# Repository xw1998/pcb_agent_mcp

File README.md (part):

# pcb-agent-mcp

**给硬件工程师和 PCB 设计者用的 MCP 服务器**：把「电路计算 + KiCad / 立创 EDA Pro 实操」接到 Claude、Cursor、Cherry Studio、Cline 等任何支持 **Model Context Protocol (MCP)** 的 AI 客户端上，让它在画板、选器件、跑 DRC、算载流与阻抗、对嘉立创（JLCPCB）工艺门禁时，给出来的是**量出来的数字**和**带闸门的写操作**，而不是背下来的经验。

> 检索关键词：PCB / EDA / MCP / Model Context Protocol / AI Agent / KiCad / 立创EDA / 嘉立创 / JLCPCB / 打样 / DRC / 阻抗 / 叠层 / 载流 / 温升 / 爬电距离 / IPC-2221 / 磁芯选型 / 环路与热 / 原理图 / Gerber。
> 全部在你自己机器上跑（唯一的出网是可选的立创在线取件查询，关掉就走本地 SQLite），零运行时依赖，Python ≥ 3.9。

> **这是 source-available（源码可见），不是 OSI 认证的开源软件。**
> **`0.1.43` 是本项目第一次对外发布。** 仓库历史里那份 MIT `LICENSE` 是内部草稿期的遗留文本，**从未对外提供过任何副本，因而不构成对外授权**；MIT 不适用于本仓库的任何版本（见文末「License」）。
> 代码按 [PolyForm Noncommercial 1.0.0](LICENSE) 授权、**禁止任何商业用途**；文档按 [CC BY-NC-SA 4.0](https://creativecommons.org/licenses/by-nc-sa/4.0/deed.zh)；随包的第三方组件各有原许可（见 [THIRD-PARTY.md](THIRD-PARTY.md)）。
> 商业授权请开 [Issue](https://gitee.com/xw19981010/pcb_agent_mcp/issues) 或邮件 <1490588966@qq.com>；细则见文末「License」。

当前版本 **`0.1.43`**：**注册 266 个工具**（`tools/list` 默认只暴露 50 个入口，全量需 `PCB_AGENT_TOOLSET=all`）、**零 runtime 依赖**、Python ≥ 3.9。已实现十一层：只读的算/保真/适配/度量/仿真，一条**带闸门的写路径**（提案 → 落盘，两种格式；还能**分步落盘**，让人在 EDA 窗口里看着它一步步长出来并随时喊停），一个**会说不通在哪**的布线器，一套**外包给立创/板厂自己的裁判**的制造输出与原理图同步，以及一层**从 20 块真实好板子量出习惯、但绝不自己动手改板**的经验累积（[docs/94](docs/94-经验累积模块与语料.md)）。
立创侧的每条口径都以 **194 个真实 `.epro` 归档**为证据（[docs/13](docs/13-立创实测-真实存储与记录格式.md)）；
KiCad 侧的几何与规则对着厂商自己核过：13 块真实板的 DRC 对账（厂商报的 56 条全命中）、
412 个焊盘与 `pcbnew` 逐点对账 0 不一致（[docs/15](docs/15-对账-推导对着厂商判决.md)）。

## 三十秒上手

```bash
git clone https://gitee.com/xw19981010/pcb_agent_mcp.git
cd pcb_agent_mcp
python run_server.py --version    # pcb-agent-mcp 0.1.43
python run_server.py              # 起 stdio MCP 服务（日志只写 stderr，stdout 归协议）
```

MCP 客户端（stdio）配置 —— 把路径换成你自己的绝对路径：

```json
{
  "mcpServers": {
    "pcb-agent": {
      "command": "python",
      "args": ["D:/path/to/pcb_agent_mcp/run_server.py"]
    }
  }
}
```

连上之后先调 **`calc_capabilities`**：它逐条列出「能算什么 / 拒算什么、为什么」，比任何文档都准，
也是本项目唯一不会过期的能力清单。完整自检与全量测试见[「用法」](#用法)。

## 本文目录

- 一页速查：做完了什么 / 还差什么
- 为什么不是"又一个图元 MCP"
- 三条诚实规则（代码里强制，不是口号）
- 为什么要内置计算：两个真实反例
- 信封契约
- 工具（266 个，默认入口 50 个）
- JLCPCB 制板门禁
- 用法
- 路线图
- 已知未实现 / 已打折扣的地方（诚实清单）
- 项目结构
- 第三方组件与商标
- 免责声明
- 贡献
- License

> **只想判断「现在能不能用」？** 直接看下面隔一节的
> **「一页速查：做完了什么 / 还差什么」**——三十秒扫完；本表是逐层机制。

| 层 | 做什么 | 状态 |
|---|---|---|
| **Calc** | 无板子的工程计算（载流/电流场/阻抗/差分阻抗/λ/20/爬电） | 已实现 |
| **Fidelity** | 把整份板文件**转换**成 AI 可读的表达：每个节点都进树，事实从树里读，往返由 KiCad 自己验证 | 已实现（KiCad 侧已被 kicad-cli 判决） |
| **Adapter** | 在保真树之上给一个 Canonical 便利视图（mm、Y 上、net 用名字） | 已实现（KiCad 侧：13 块真实板与 DRC 对账、412 个 pad 与 `pcbnew` 逐点对账；立创侧：194 个真实归档实测） |
| **Oracle** | 在解析出的板子上做度量（clearance / free_space / 铺铜连通 / 跨分割 / 环路面积 / 单网 IR drop） | 已实现 |
| **Sim** | 无板子的物理计算：SPICE 子集（DC/瞬态/AC）、铜阻与 PDN、热阻与 2-D 板温度、薄板模态与振动响应、平面谐振、电热耦合（单集中 Rth） | 已实现（子集，未实现项逐条点名拒绝（`0.0.37` 起 `A` 卡由随包 ngspice 承担；`0.0.39` 起 `gain`/`limit`、`0.0.40` 起多端口的 `summer`/`mult` 这四种代数 code model 由内置自己解） |
| **Desktop** | 找得到/启得动/关得掉 EDA，能打开工程并用窗口标题确认 | 已实现 |
| **Write** | `propose`（只算不写）→ `apply`（checkpoint + 原子写 + 六道闸门 + 失败回滚） | 已实现（KiCad 真机验证；`.epro` 实测口径＝原地重写一个成员，`0.0.62` 起**写出的归档再喂回应用并回读几何**验证过；`0.0.95` 起 **40 个 op**：`set_zone_params` 改铺铜的**填充参数**（`filled_areas_thickness` / `clearance` / `min_thickness`）并作废旧填充；`delete_copper` 按 net / layer / region 批量清铜；`dry_run` 走同一条写入+门禁+还原的路径试穿一次；DRC 差集的**两半对着同一份 `.kicad_pro`** 读——同一份字节，旁边没有工程文件时 515 error、有工程文件时 0 error，见 [CHANGELOG 0.0.95](CHANGELOG.md)） |
| **Route** | `board_route`：A* 布线（双栅格 + 精确多边形判决 + 事务化 + 按位置 rip-up），规则只从板/工程/调用方取，取不到就拒绝 | 已实现（50 网真板 baseline 27/50 → sweep+rip 38/50、端到端 apply 后 kicad-cli DRC 0 新增阻断项、12 网提速 5.5×；`0.0.15` 起爬电/差分对间距/等长进搜索，`0.0.16` 起回流/阻抗目标/拥塞协商也进了（协商默认关，一块板 +3 网 / +61% 时间），`0.0.17` 铺铜重填与多端网拓扑，`0.0.18` 起布不通要报**挡路的是谁**（`board_blockers`）与**哪些球埋着**（`board_fanout`）；`0.0.90` 起**锁定的铜不动**（文件里的 `(locked)` 或调用方的 `fixed_nets`：不布、不撕、不耦合/不等长——那两个 pass 要 MOVE 铜，所以是**拒绝**而不是悄悄剔掉，且无铜的固定网报 `fixed_missing_copper`），写路径对锁定铜要 `allow_fixed=true` 才动；`0.0.91` 起**悬空铜可查可切**（`board_dangling_copper`：只在「一个附着点 + 不是任何 pad 的唯一铜」被证明后才切，浮铜默认不动、锁定铜一律不动、没铺铜 fill 就如实说不猜；`0.0.92` 起在真板上把它的前提修对——通孔焊盘跨层、底面不镜像，并加 `pad_trust` 闸门：焊盘位置是推导时只列候选不判可切），仍然四邻 + 4×45°、不拆已接受的扇出、拓扑默认 mst 且不是精确 RSMT） |
| **Fab** | 制造输出：Gerber / Excellon / 位置文件 / gbrjob / STEP / PDF / BOM / 网表 / 图形，加 `manifest.json` 与可选 `fab.zip` | 已实现（**只外包不重算**：`kicad-cli` 在临时目录里跑，产物**重新读一遍**验终止符 / 工具表 / 行数 / ISO-10303-21，不合格判 failed；真板 15 个产物 / 103 923 字节 / `fab.zip` 33 577 字节；`out_dir` 落在源目录里直接拒） |
| **Sync** | 原理图网表 ↔ 板：逐脚差集，再变成 op 交给写路径 | 已实现（两侧都用权威：KiCad 自己的网表器 + 板文件里的 pad net；缺封装只报 `needs_placement`，**没有诚实的默认位置**；`sync` 一个字节都不写） |
| **Experience** | 从真实好板子量出来的经验：`hard`（违反＝缺陷）/ `soft`（违背＝问一句）两条链，7 个闭集度量，候选永不自己升级 | 已实现（种子 7 条 active 随包发出：6 个真实工程、20 块板、16 522 段铜、12 805 个 via；数字由判板子的同一份代码量出；改板一条都不做。[docs/120](docs/120-方案与布局的积累.md) 起补上**入料口**：`experience_harvest` 用同一份代码量一块板，把读数写进 `observations`、把与 active 习惯相反的写成反例候选（本机实测：4 条观测、1 条反例），`experience_status` 报「几条 active / 几条候选没人确认 / 文件最后写入时间」——库活着还是不活着，从此是读数不是印象） |
| **Layout quality** | 布局的**连续**读数（间距节奏/朝向/对齐/留白/密度/簇分离），给参考集时给分位 | 已实现（[docs/121](docs/121-布局质量与拓扑.md)：因为 `board_drc` 只有通过/不通过，在「勉强合规到正常」那一片里判据是平的、没有梯度——`docs/117` 那块 clearance 0、isolated 0 却两面地之间**零缝合孔**的板就是证据。分位只在给了参考集时出现；无方向指标只报分布位置不报好坏；**参考集是同族副本时判不可用**（本机 3 个备份版本实测） |
| **Topology** | 先分区后坐标：谁和谁同一功能组、组间怎么连、电源往哪流 | 已实现（[docs/121](docs/121-布局质量与拓扑.md)：主控按焊盘扇出认（本机 `PA0/PA11/+3V3` 这种网名任何关键词表都盖不住），其余按网名命中数投票；只碰电源轨的算电源；认不出的就近并入（≤15 mm）否则如实列 `unclassified`；`flow` 从 power 做广度优先，连不上的报 `unreached`） |
| **Pour fragments / corner fitting** | 铺铜被切成几块、每块多大、相邻隔多远；以及「切角会撞到邻居时是跳过还是缩短」 | 已实现（[docs/124](docs/124-铺铜碎块与自适应倒角.md)：新增 `board_pour_fragments`（鞋带面积 + 最近顶点对间距，未灌铜报 `pour_not_filled` 而不是 0 块），`board_angle_audit` 的 `chamfer` 加了 `adaptive`（撞了就二分缩到最大可行切角，实测同一块板 5→7 个切角、2 个从 1.0 缩到 0.25）。实测数据：+3V3 的 8 个形状块灌铜后是 **14 块**，最大 15.37×2.30 mm、最小 0.44×0.70 mm，最近邻 8 mm —— 这是「靠铺铜连通 3.3V」在这块 2 层板上不成立的直接原因。工具不判断两块能否连，只给几何。第三件：`board_routability` 加 `width_scan_mm` 线宽阶梯，回答「最宽能出去多少」——同一块板上 U1.14/19/21 只能 **0.3**、P2.3/P2.5 只能 **0.25**，这就是「+3V3 全程 0.4」在这里被推翻的数字依据；顺带一条被测试纠正的错判：三面围铜不吃线宽，**走廊**才吃） |
| **Via legality** | 一个孔**法律上**放得下吗、余量多少、被什么挡住 | 已实现（[docs/126](docs/126-过孔选址.md)：`board_via_sites`。缝合那轮的代价是量出来的——16 个接地孤岛只有 4 块放得下 0.45 孔，其中 2 块撞进 PD13/PD14 走线，靠重建板子读 DRC 才发现。`net` 是关键参数：该网自己的铜不吃余量（孔就长在自己的线上），但钻孔间距是工艺规则、任何网都不豁免。`room_mm` = 最紧那条约束的余量，`limited_by` 指名是哪条。真板实测：U1 上边扇出处 441 个候选里 **16 个**合法、最大余量 0.325 mm（限制来自邻线，不是铺铜），下边 **40 个**/0.225 mm。铺铜**默认不算障碍**（灌铜会绕开新孔重切，孔落在别网平面上只是咬掉一块），但每个点报 `inside_pours` 说明会咬哪块；`pours_block=true` 恢复严格口径。不放置、不写板） |
| **Trunk feasibility** | 这一网的焊盘簇之间，主干到底**能走多宽**、卡在哪一格 | 已实现（[docs/127](docs/127-电源干线可行性.md)：`board_trunk_plan`。因为「38 个 +3V3 未连接」能报，「0.4 主干走不走得过去」没人能答——那时只能先猜 0.5、被 DRC 打回、再猜 0.3。做法：焊盘**单连接聚类**（一排焊盘是一块，不是 20 个零长走廊）→ 簇心最小生成树 → 每条边两侧 `band_mm` 栅格化，每格价值 `2·min(到别网铜 − 间距, 到板边 − 边距)` → 带内**最大瓶颈路径**（可绕开焊盘排、不可穿过），4 连通。真板 sky_star `+3V3`：45 焊盘 → **14 簇 13 条边**、单次 **9.2 s**，0.4 mm 主干在 **12/13** 条通道上有层能走（`track_mm=0.5` 就变 2 条不通）；最薄 `9->13` F.Cu **0.164**、`11->12` F.Cu **0.373**（改走 B.Cu）；`5->9` **双层封死**，`grid` 0.15 / 0.12 与 `band` 8.0 三次复核仍 `no_path`——那 18.19 mm 走廊里实有 509 段信号线、30 焊盘、15 过孔，该动布局不是走线。**粗栅格把宽度读窄**：`9->13` 在 0.25/0.15/0.12 下是 0.164/0.314/0.345，最坏丢 `≈0.7·grid`，所以细一档是复核手段；超出 `band_mm` 就什么都不说，`beyond_reach` 是上界不是测量值。不写路径、不选层） |
| **Teardrop room** | 每个焊盘角上**还有没有位置**放泪滴、最长能长到多少 | 已实现（[docs/128](docs/128-泪滴余量与最长泪滴.md)：`board_teardrop_room`。参考工程的 `PRIMITIVE/TEARDROP` 对象有 30 个，照着复刻的 sky_star 一个都没有——「照着画不像」里可量的就是这个。做法：走线端点落在同网焊盘上、且**另一端在焊盘外**才算角 → 方向取**走线自身**（不是质心连线）→ 起点取中心线**离开焊盘**那一点，宽度取该点的**弦** → 两条斜边与端帽按 `grid_mm` 采样，每点 `min(到别网铜 − 间距, 到板边 − 边距)`，最小值为 `room_mm`（负数是「放不下多少」），并指名卡住它的对象；`max_length_mm` 是整条包络仍合法的**最长长度**（0.1 mm 步进）。**同网铜不是障碍**（泪滴就长在自己的铜上），障碍集按网过滤。真板：**238 个角、234 个放得下、4 个不行**，默认 `limit=40` 单次 **5.2 s**；最紧 `R19.1` `room −0.100`（与 `+3V3` 只隔 0.05）。`pad_width` 是离开焊盘处的弦不是对角线——按对角线会把 45° 引出的 0.3×1.6 焊盘读成 1.6 宽、一整排排针判死。不画泪滴、不选 curve） |
| **Net gaps** | 一个网的铜**断成几块**、最近的两块**差多远、在哪一段** | 已实现（[docs/129](docs/129-网络的铜断成几块.md)：`board_net_gaps`。DRC 只给「unconnected 115」这一行总数，它数 ratsnest 边，不会说 `+3V3` 一个人占 38 条、断成 39 块、最近两块只差 0.05 mm。做法：把这一网的焊盘/走线/过孔**加上它自己铺铜的 filled_polygon**（`_items` 里没有铺铜，而铺过铜的板子最大的那一块铜就是它）当几何 → 段级并查集（走线的圆头宽度、多边形取边）→ 触碰/重叠/包含即连通 → 报每块的焊盘位号/包围盒 + 相邻两块的最小边到边距离和量它的那对线段。不给 `net` 就数全板，这就是与 DRC 的对照：`+3V3 38/38、AGND 9/9、$2N1188 6/6、VDDA 5/5` 全等，**GND 不等（4 vs 15）**——差的 11 条是只靠单个焊盘散热辐条挂住的铺铜岛，我的几何算一个导体、KiCad 不算，因此**过不过板子听 DRC，这个工具只回答在哪、差多远**。真板 `+3V3` 0.55 s、全板 1.65 s。不连线、不换层、不挪件） |
| **Cut-line capacity** | 一条线切下去，两半之间有几条通道、又有几条网**必须**跨过去（布局层面成不成立） | 已实现（[docs/125](docs/125-切线容量.md)：`board_cut_capacity`。「必须过的网数 > 通道总数」是画通不了的必要条件，不必等布线器。默认只数画出来的铜（焊盘/过孔/走线），**不算铺铜**——灌铜会绕着过去的线重切，算进去会让每条铺过铜的线都读成满；`sensitivity` 三档把这份代价摆出来。实测 sky_star：排针列 361 条通道 对 5 个必须过的网，**推翻了我自己「12 个网穿焊盘行是通道不够」的解释**——差两个数量级，堵点在焊盘逃逸宽度。不选网、不画线） |
| **Routing discipline** | 走线的**形状**（斜线/离网格/跨板长段/拐角/扇出）、**规矩**（线宽梯级与按角色取宽、过孔族、拐角风格）与**重画清单** | 已实现（[docs/122](docs/122-布线纪律与参考板距离.md)：3 个工具 `board_routing_profile` / `board_house_style` / `board_routing_violations`。实测被参考板推翻了三个假设——F412 的斜线占比 44% 低于生产板的 48%、绕行率 1.089 优于 1.258、拐角 96% 已是 45°；唯一巨大的差异是线宽梯级 1 级 vs 13 级。`board_house_style` 从参考板取**比例**不取毫米（0.10 mm 信号线不是 53 mm 板子的宽度），`clearance_room` 逐网给出「最宽能到多少」，加宽不了进 `blocked` 并说明要先挪邻居；差分对同宽。三者都不写盘、不布线） |
| **Patterns** | 已经做成过的**方案**（recipe：让某件事 work 的参数与步骤）与**布局**（layout：相对一个 anchor 的毫米偏移） | 已实现（[docs/120](docs/120-方案与布局的积累.md)，6 个工具：`pattern_add` 只写 candidate；`pattern_verify` 要 `confirm=true` + 理由 + 一条带 `from`/`reading` 的证据；参数不给来源直接拒；布局必须恰好一个 anchor；`pattern_layout_plan` 只算坐标并报冲突（越界 / 同一位号已在板上 / 小于 `min_gap_mm`），**不写板**——本服务没有自动布局，这是禁令不是待办） |

写路径的三条硬规则：**提案不落盘**（plan 单次使用、1 小时过期）；**落盘要 `confirm=true`**；
**闸门不信任写代码本身**——KiCad 侧是盘上字节、token 双射、每条 op 的后置条件、`kicad-cli` 的
stats/Gerber/贴片坐标比对、以及 **DRC 差集**（新增违规就拦下并回滚）；立创侧是写盘字节、其他成员
逐字节不变、未点名行不变、流仍可解析、改动恰好等于计划、重新解析后事实成立。
KiCad 侧这套闸门在自造示例板上真拦下过三次错（丝印压板边、悬空走线、悬空过孔）。

> 设计文档在 [`docs/`](docs/)，按编号顺序读：
> `00` 调研与架构 → `05` 无损转化架构总纲 → `06` 存储形式与信息传递 → `07` 自研定位与风险分期
> → `10` 桌面控制与双栈读路径 → `11` 保真层 → `12` 写路径 → `13` 立创实测（真实存储与记录格式）
> → `14` 原理图写路径 → `15` 对账（推导对着厂商判决）→ `16` 天线与馈线 → `17` 仿真层
> → `18` DFM 工艺能力校验 → `19` 机械振动（薄板 Ritz 模态、多模态随机响应、Steinberg、冲击、传递率）
> → `20` 平面谐振与电热耦合 → `22` 微带与腔体滤波器 → `24` 立创进程内桥
> → `25` 技能并入清单 → `26` 分步可见与铺铜闭环 → `27` 自动布线器。

## 一页速查：做完了什么 / 还差什么

这一节回答一个问题：**现在能不能用、哪一格还不能信。** 三十秒扫完；机制与数字在下面
「已知未实现 / 已打折扣的地方」与 `docs/` 对应篇目里。

判定口径只有一条：一个能力同时满足 ① 有工具 ② 有闸门或参照 ③ **有一条能失败的对照**
（负控制，或对着厂商判决的对账）才算「做完了」。只写了代码、没有对照的，一律算没做完。

### A ｜做完了（有工具、有对账、边界写在每次返回里）

| 能力 | 起于 | 凭什么说做完了 | 它自己的边界 |
|---|---|---|---|
| **工程计算**：载流 / 阻抗 / 差分 / λ/20 / 爬电 / 间隙 / 铜阻 / 电感 / 链路 | `0.0.1`，真实表 `0.0.10` | IEC 60664-1 阶梯从 KiCad 10.0 原实现反演，**188 528 点 0 失配**（32 键 / 808 步）；IPC-2152 用 Brooks & Adam 闭式 + 3 个独立锚点复现 | 闭式近似，误差进 `precision`；IEC 62368-1 / 61010-1 / UL 60950 / IPC-2221 仍 fail-closed |
| **二维场解**：差分截面 / 共面单线 / 共面差分对 / 有限宽地 / 导体损耗 | `0.0.19`~`0.0.26` | 零厚度带状线对精确共形解 ≤1.2%、孤立微带对 Hammerstad ≤2.8%；共面差分对无闭式，改用叠加恒等式（残差 1.9e-8）+ 奇模电荷平衡 −1.000000000 + 极限 | 紧间距耦合**没有独立参考答案**（回 `reference_note`）；铜厚只划网格不建模；共面解比闭式**读低 1.19%~3.39%** |
| **保真层**：整份文档进树，往返可证 | `0.0.1`（`0.0.18` 补口径） | KiCad 侧 token 双射 + 逐字节往返；立创侧 194 个真实 `.epro` 归档实测 | 13 块 demo 板覆盖不到的少见语法可能没走到 |
| **Adapter**：两份格式 → 一个 Canonical | `0.0.1` | 13 块真实板上与 `kicad-cli 10.0.7` 对账（厂商 56 条 recall 1.0）、412 pad / 20 188 次 HitTest / 0 不一致 | 立创焊盘位置是推导（顶面 62.1% / 底面 82.6% 落在本网铜端点上，是**下界**不是精度）；底面**不镜像**（`-y` 只有 37.0%/53.2%，异网误撞 1/2） |
| **Oracle 度量**：间距 / 可放空间 / 铺铜连通 / 跨分割 / 环路 / IR drop | `0.0.1` | 每条带 `authoritative:false` + 裁判在哪；能对账的间距项双向数 recall 与 extra | 三类几何**不建模**（zone 铜、板边与孔规则、阻焊钢网）；比不了的明确 `not_comparable` |
| **写路径**：提案 → 落盘 → 闸门 → 回滚（两种格式） | `0.0.1` | KiCad 五道闸门（含 DRC 差集）在自造板上**真拦下过三次错**；立创六道闸门，实测同一工程两次保存只改一个成员 | 立创原理图 `.esch`、SQLite `.eprj2` 一律拒写 |
| **原理图**：KiCad 单页 22 op + 多页 4 个 sheet op | `0.0.1` / `0.0.33` | 裁判换成 KiCad 自己的网表 + ERC 双向 diff；页号按**工程全局**分配 | 不做跨多文件原子写、页面模板、搬文件、批量重命名 |
| **布线器**：A* + 精确多边形判决 + 事务化 + 按位置 rip-up | `0.0.14`~`0.0.17` | 50 网真板 27/50 → 38/50（开协商 41/50）；端到端 apply 后 `kicad-cli DRC` 新增阻断项 = 0 | 四邻 + 4×45°、不拆已接受扇出、拓扑非精确 RSMT、拥塞协商默认关 |
| **制造输出与同步**：Gerber/Excellon/STEP/PDF/BOM/网表 + 原理图↔板差集 | `0.0.18` | 产物**重新读一遍**验终止符/工具表/行数/ISO-10303-21；`out_dir` 落在源目录里直接拒 | 只外包 `kicad-cli`，不重写 writer；`schematic_pcb_sync` 一个字节都不写 |
| **仿真（内置 SPICE）** | `0.0.7` 起，`0.0.27`~`0.0.39` 逐类长出来 | 器件 `R C L V I E G F H K D Q M B S W J` + `X`/`T`/`O`/`U` + `.noise` + `A` 的 `gain`/`limit`/`summer`/`mult`，每类都有对账（例：1 kΩ 读 `4.071372237e-09 = sqrt(4kT·1000)`） | 后向欧拉；无自热、无失真/傅里叶、无器件电容随温度；`A` 里只有四种纯代数 code model 进内置；1/f 只做**二极管**（`KF*|Id|^AF/f`，`Q`/`M`/`J` 的 `KF=` 在 `.noise` 按名拒答），`mc(...)` 这类统计值一律拒答，`.temp` 多值是扫描（`0.0.54`） |
| **仿真（外部引擎 + 随包）** | `0.0.7` → `0.0.37` 随包 | 真 ngspice-47 逐节点对账（分压 5e-9 V）；随包副本与系统副本六类 deck 差 0 ~ 1 ulp | 只 Windows x86_64；`engine="auto"` **刻意不看随包**；不做 DLL 进程内 |
| **热 / PDN / 振动 / 平面 / 电热** | `0.0.5`~`0.0.6`、`0.0.10` | 2-D 板温度 `73.393487 ℃` 对闭式 `73.39345`；Ritz 模态 SSSS 330.385 Hz、CCCC 602.382 Hz 与解析解吻合 | 1-D/2-D 稳态、薄板单模态、平面只有模频与导体/介质损耗的 Q 上界、电热单集中 `Rth` |
| **铺展（收缩）热阻**：板上的小焊盘比它自己那柱铜多出多少 | `0.0.85` | 两个极限是**手算恒等式**：整板 `t/(kA) = 0.05` 精确、对流整板 `0.05 + 1/(hA) = 10.05` 精确；另有一个**不分离变量**的三维 FVM 在 `dz` 逐档减半时差距 12.42→8.29→4.13→2.03→0.97 % 逐档减半；四条负控制（漏正交因子 >10 %、整板锚点对同一错法差 `0.0` 即**盲**、尺度错 >40 %、朴素径向式 >30 %） | 均匀热流而非等温焊盘（半空间上 8 %）、四侧绝热、单层平板；圆/环源、多层叠、热过孔、接触热阻、侧边对流都不在；薄板收敛慢（`t=1e-3 mm` 时 120 项仍差 0.85 %，答案随附 `convergence_rel`） |
| **熔断的潜热**：Onderdonk 只算到铜「到达 1083 °C」，可它还没熔 | `0.0.86` | 闭式 `β = L_f/(c(234+Tm)ln(ratio))`，几何/面积/`ρ20` 全消掉 ⇒ `I²t` **+25.3 %**、电流 **+11.9 %**（25 °C；0 °C +11.3 %、100 °C +14.0 %）；**不是**教科书的 `L_f/(c ΔT) = 0.512`——潜热阶段站在最热点上，`β/naive = (234+Tm)ln(ratio)/(Tm−Ta) = 2.0244`；五档 β 由**独立 RK4 积分同一条 ODE** 校验（相对差 1.8e-12 / 2.6e-15 / 1.5e-12 / 4.9e-12 / 2.6e-12）；`c=385` 由 `(cρ/ρ20)(234+25)` 与 `1/(CMIL²·33·ln10)` 的 **+1.34 %** 一致性定（400 会推到 +5.3 %） | 默认**关**（`melting_model="sensible"`），以前打印的熔断表**逐位不变**；`repetitive_pulse_rating` 的潜热已在 `0.0.87` 做掉，`fusing_current_taper` 在 `0.0.88` 做掉（每节点焓状态），所以三个熔断工具都带它；熔化后的体积变化与熔流、焊点合金化仍然都不在（`not_implemented_yet` 已从此前的「Melting, by name」改写为「Melting, past the melt-through」） |
| **脉冲串的潜热**：一串脉冲上的潜热，以及「可持续电流」原来答错了 | `0.0.87` | `repetitive_pulse_rating` 原来把 `i_crit = sqrt(A·h·P/(duty·β·rho))`（纯**速率平衡**，不含热容也不含熔点）当成「最大可持续电流」放在 `value` 里返回；0.0.87 把 `value` 改成真正的**不熔电流**（二分到峰值 1083 °C）：0.5 mm/1 oz/1 ms/5 % 是 **29.617434 A**，旧值 **33.156444 A**；**duty 1 %** 时旧值 **23.445147 A** 对新值 **5.284344 A** ⇒ **高报 4.436718 倍**。三段电流并存：`max_current_without_melting_a`（与潜热无关）、`max_repetitive_current_a`（旧值原样保留 + 明确标 *upper bound*）、`max_current_without_melt_through_a`（峰值可钉在 1083、靠停歇排空储层：A **29.717885** / C 5.581757 / D 5.881642，对不熔电流 **+0.34 %~+11.3 %**）。潜热在串上的效果：`latent_rise_k = L_f/c_p = **542.077922 K**`，0.95×runaway 处 81→**139** 发（+71.605 %）、274→**467**（+70.438 %），1.005×value 处 218→**2360**（+982.569 %），1.02×value 的 C/D **永不熔**；储层按**熔点处吸热速率** `φ = a(1+β·dTm) = 2155.3238 K/s` 灌满（`a = 423.8640 K/s`），绝热档的**额外通电时间** `(L_f/c_p)/φ = **0.251506 s**`（实测 0.05 s→5 发、0.01 s→25 发、0.005 s→51 发） | 默认**关**（`melting_model="sensible"`）时信封**逐位不变**（整信封相等有测试）；临界点逐发在 **1/n** 上收敛（B 组要 1e5 发）⇒ 解析值用**不动点二分**并与逐发暴力实现交叉验证；`max_repetitive_current_unaffected_by_latent=true` 是**真的**（它本就不含热容，潜热改不了它）；`fusing_current_taper` 的潜热在 `0.0.88` 补上；无 Stefan 前沿、无熔流与体积变化、无焊点合金化 |
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
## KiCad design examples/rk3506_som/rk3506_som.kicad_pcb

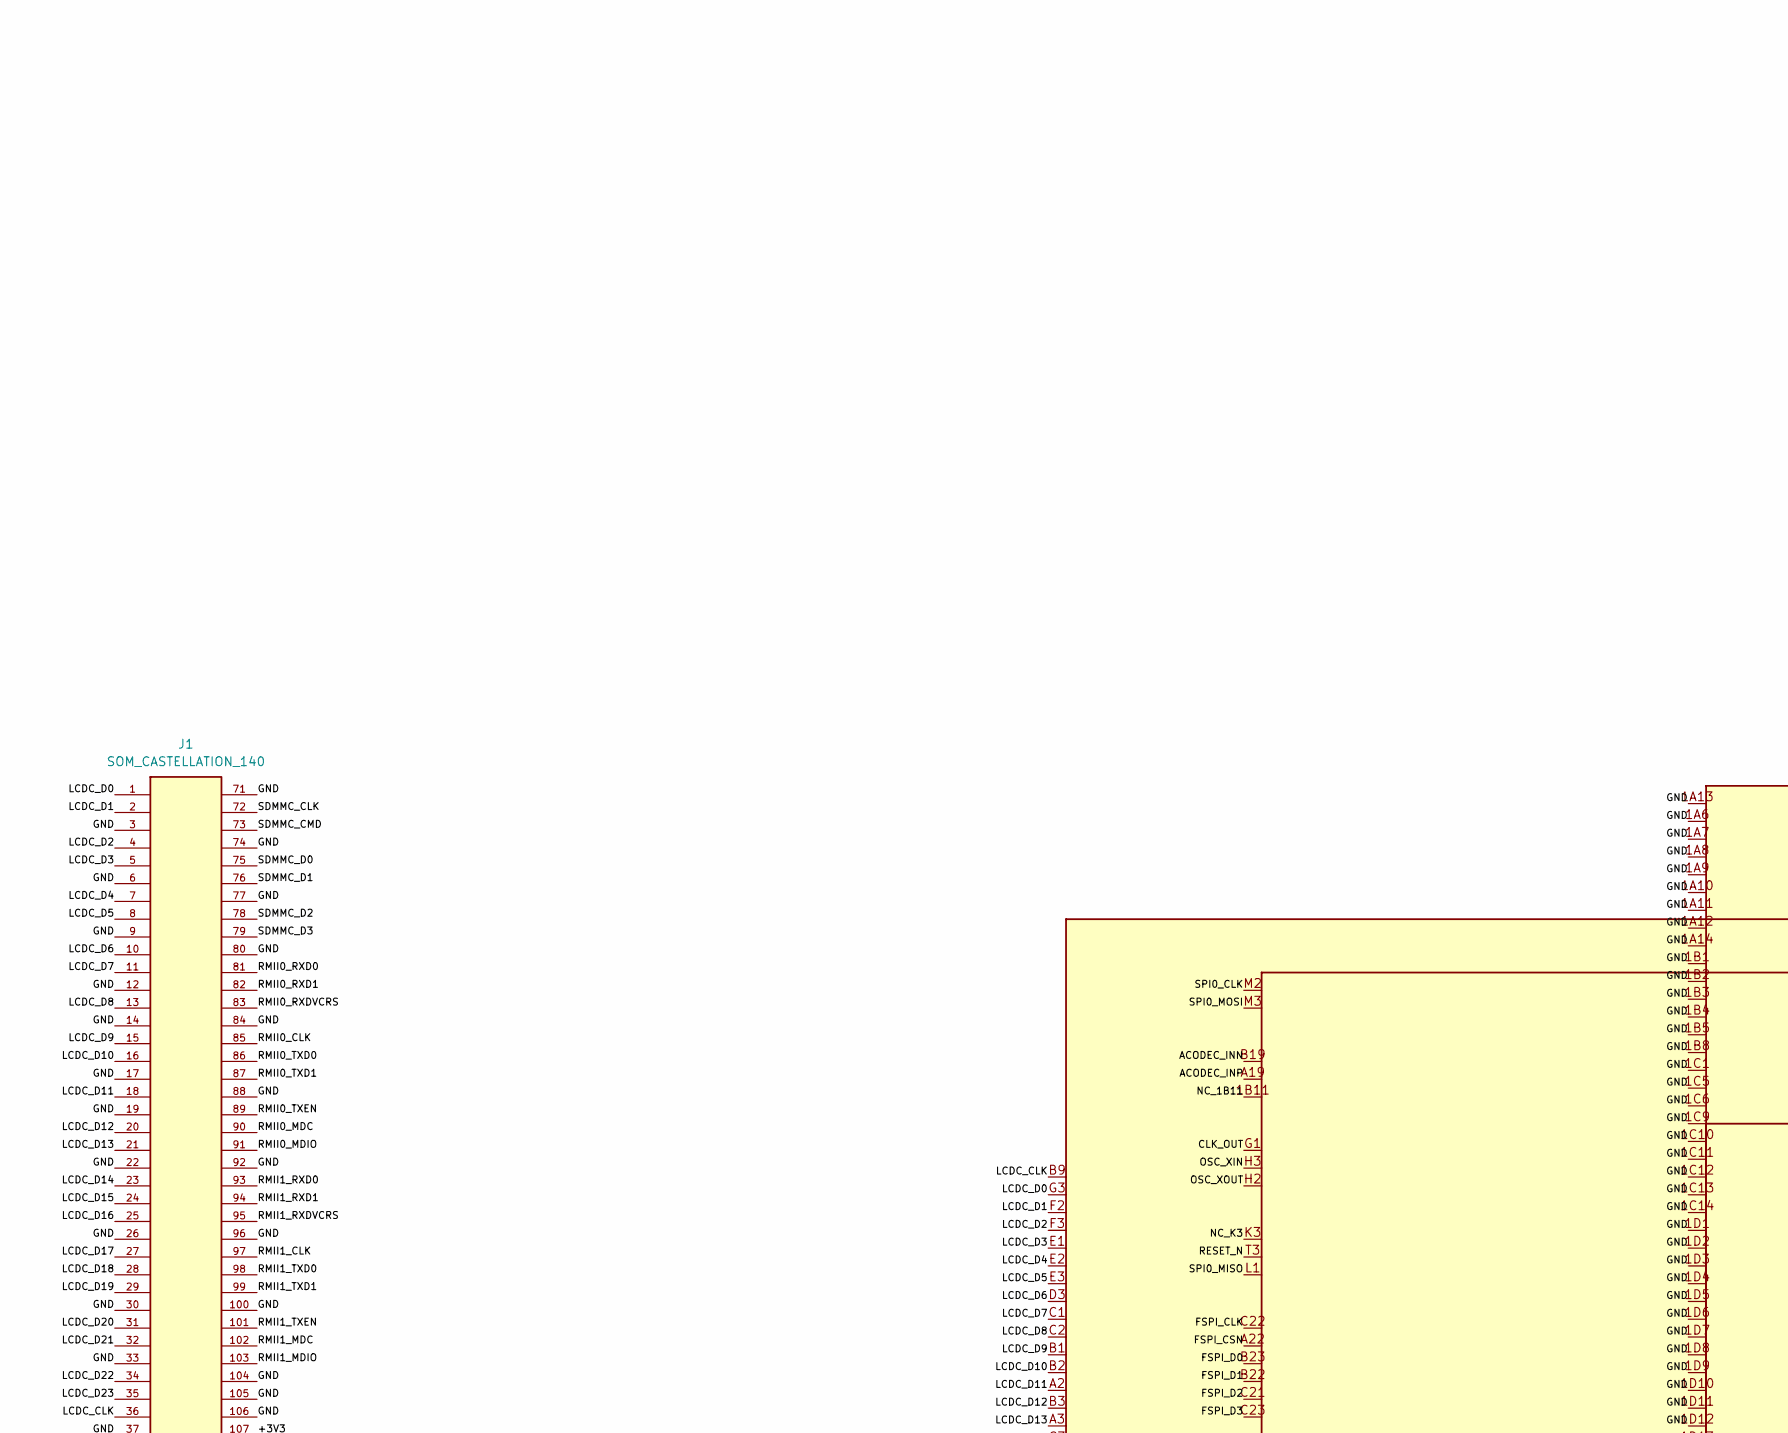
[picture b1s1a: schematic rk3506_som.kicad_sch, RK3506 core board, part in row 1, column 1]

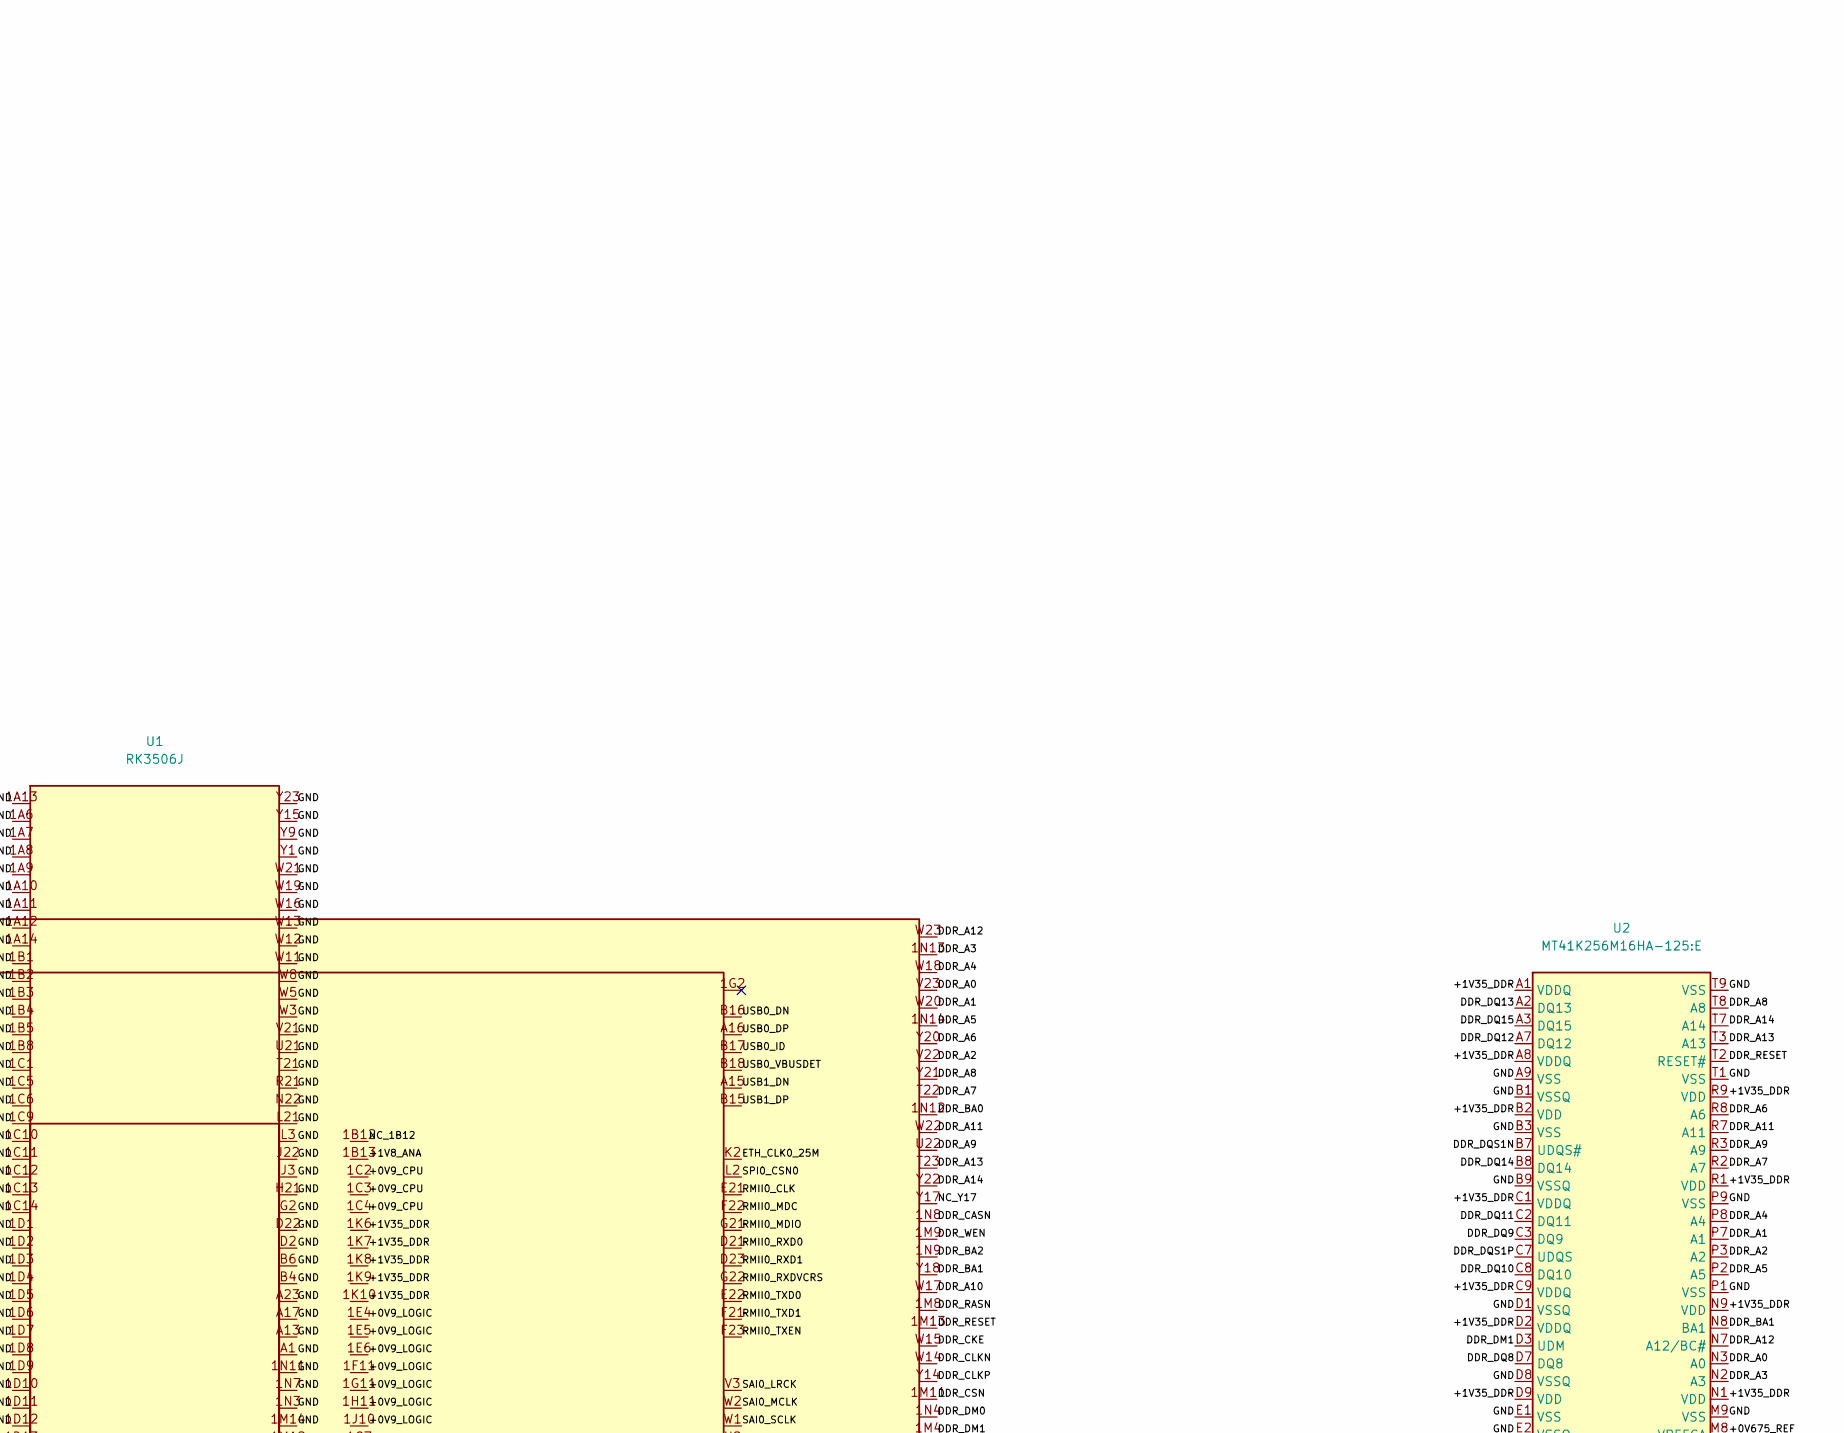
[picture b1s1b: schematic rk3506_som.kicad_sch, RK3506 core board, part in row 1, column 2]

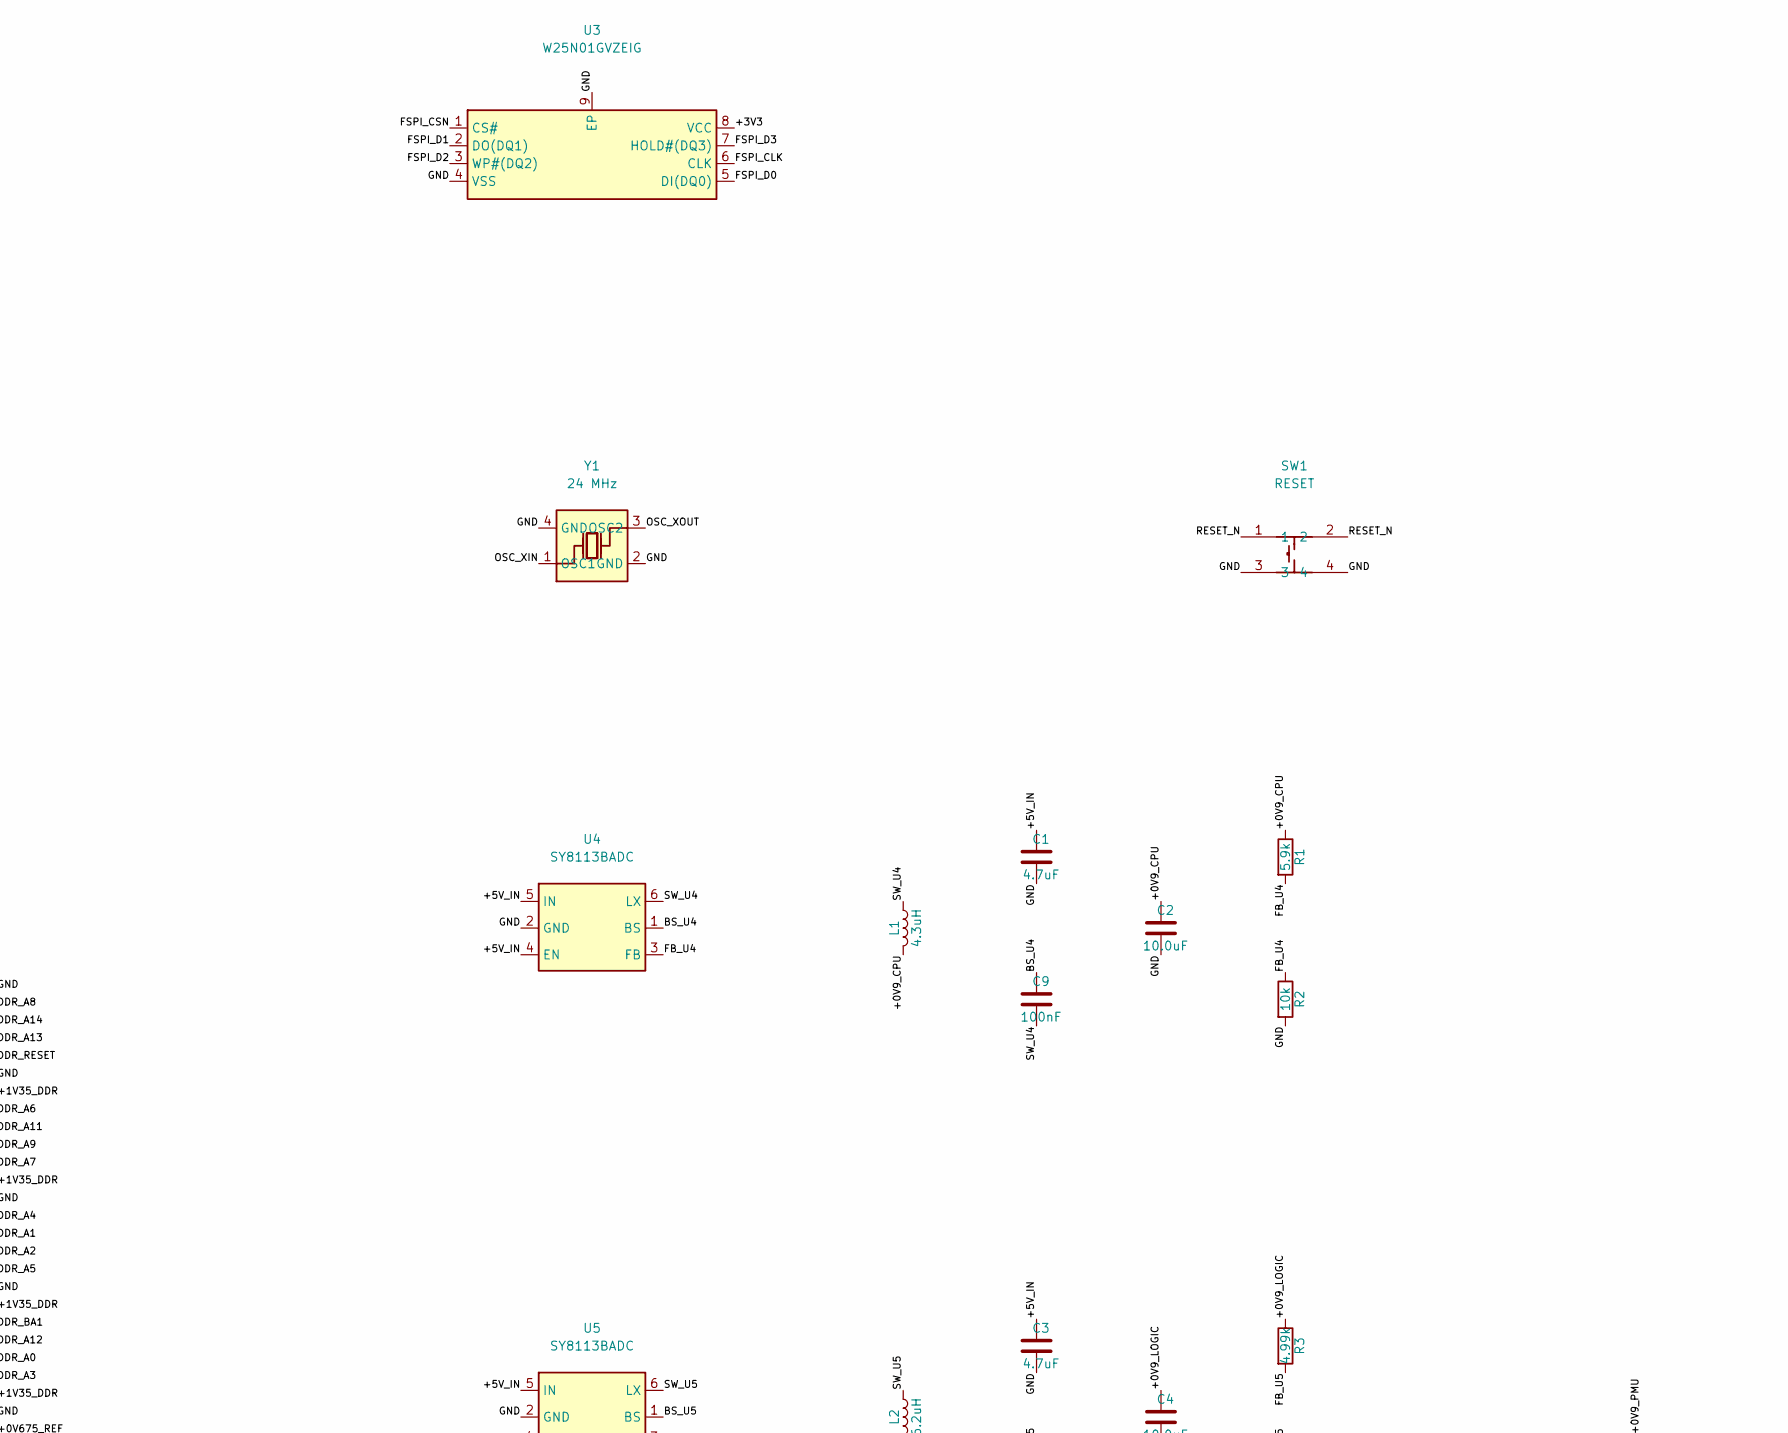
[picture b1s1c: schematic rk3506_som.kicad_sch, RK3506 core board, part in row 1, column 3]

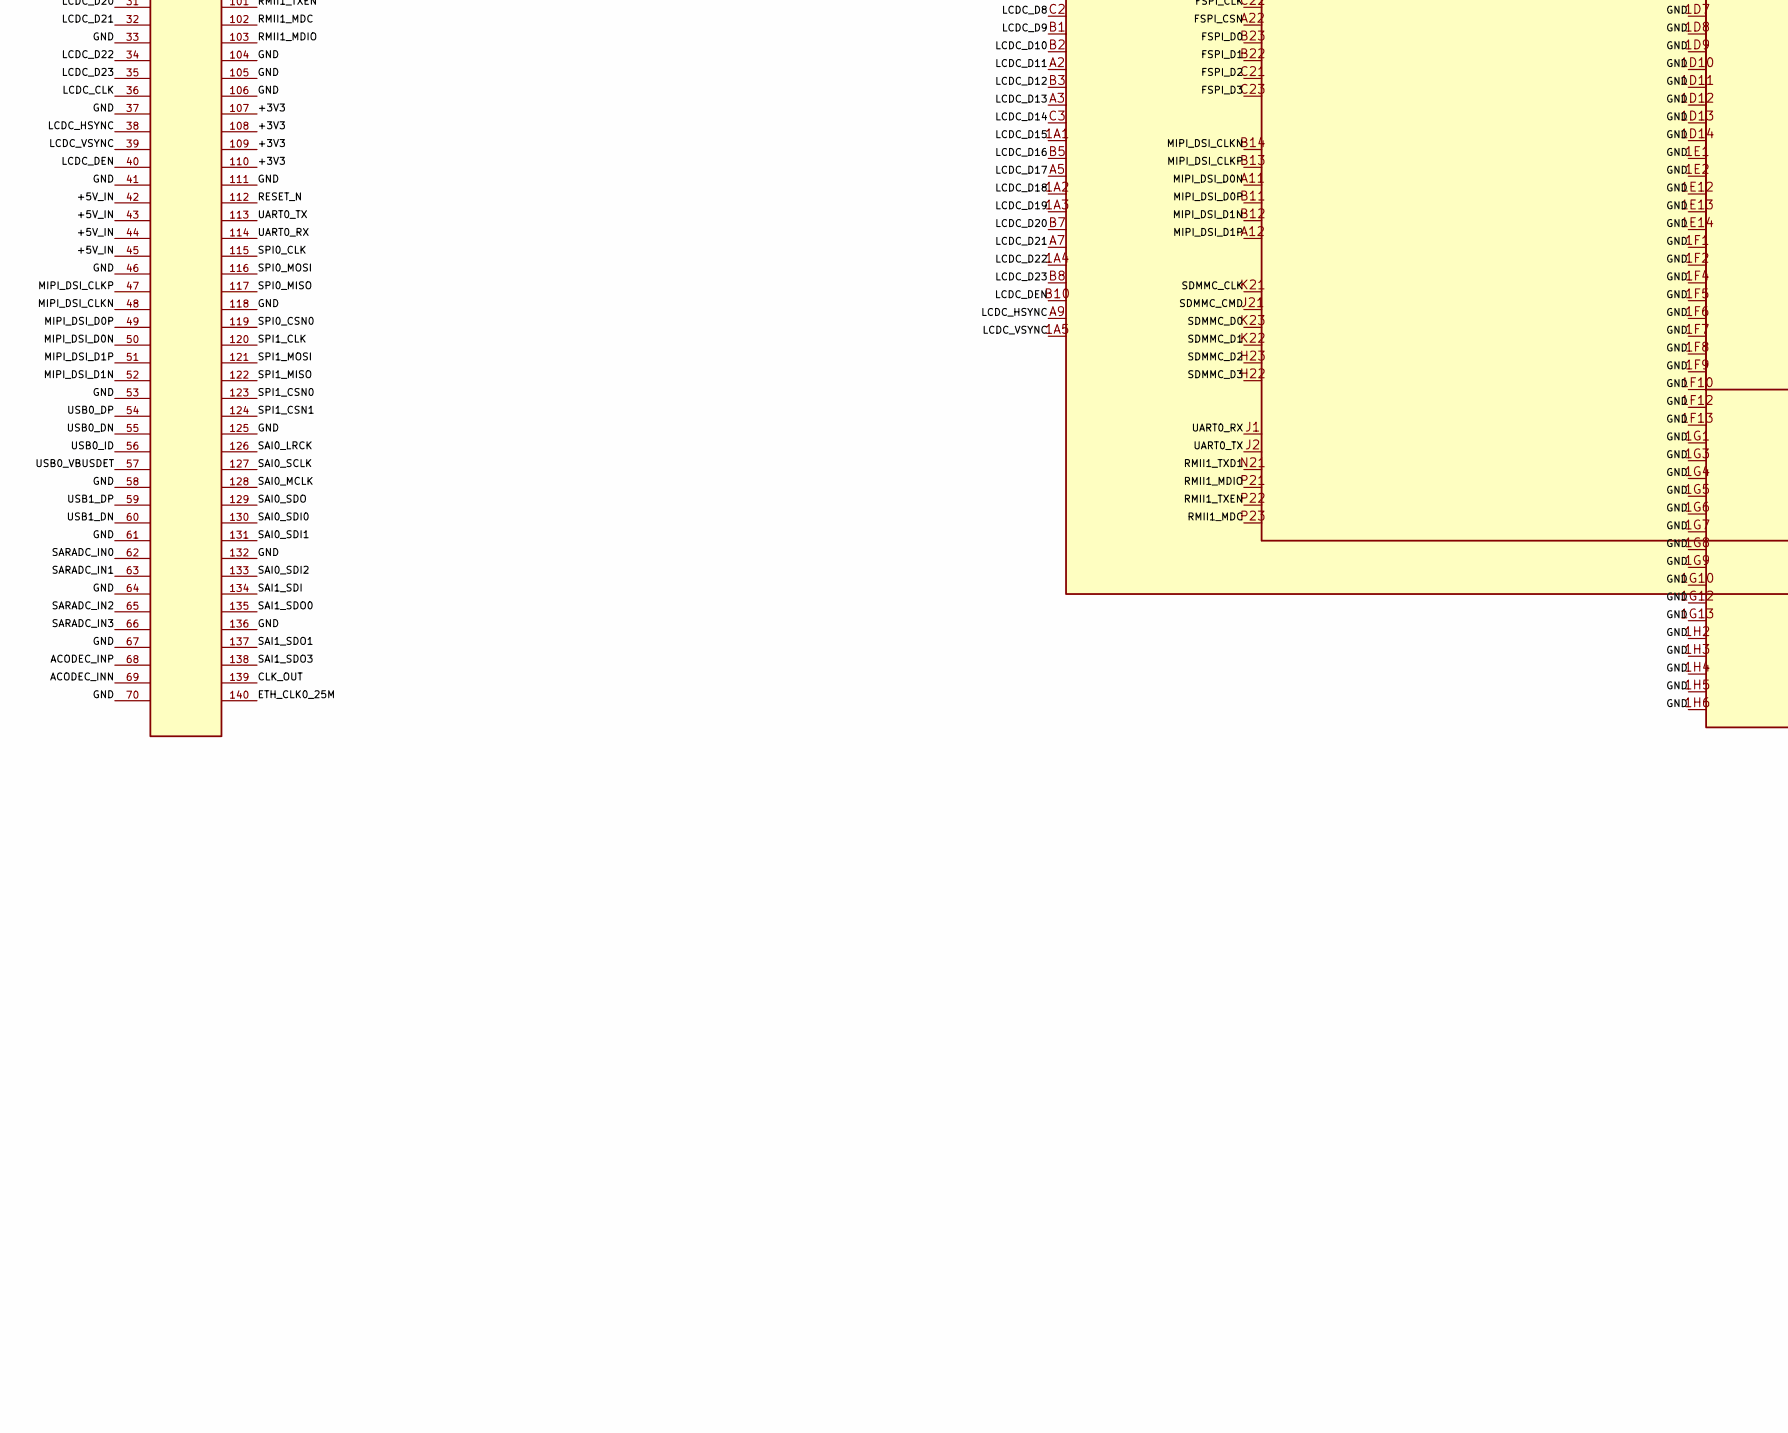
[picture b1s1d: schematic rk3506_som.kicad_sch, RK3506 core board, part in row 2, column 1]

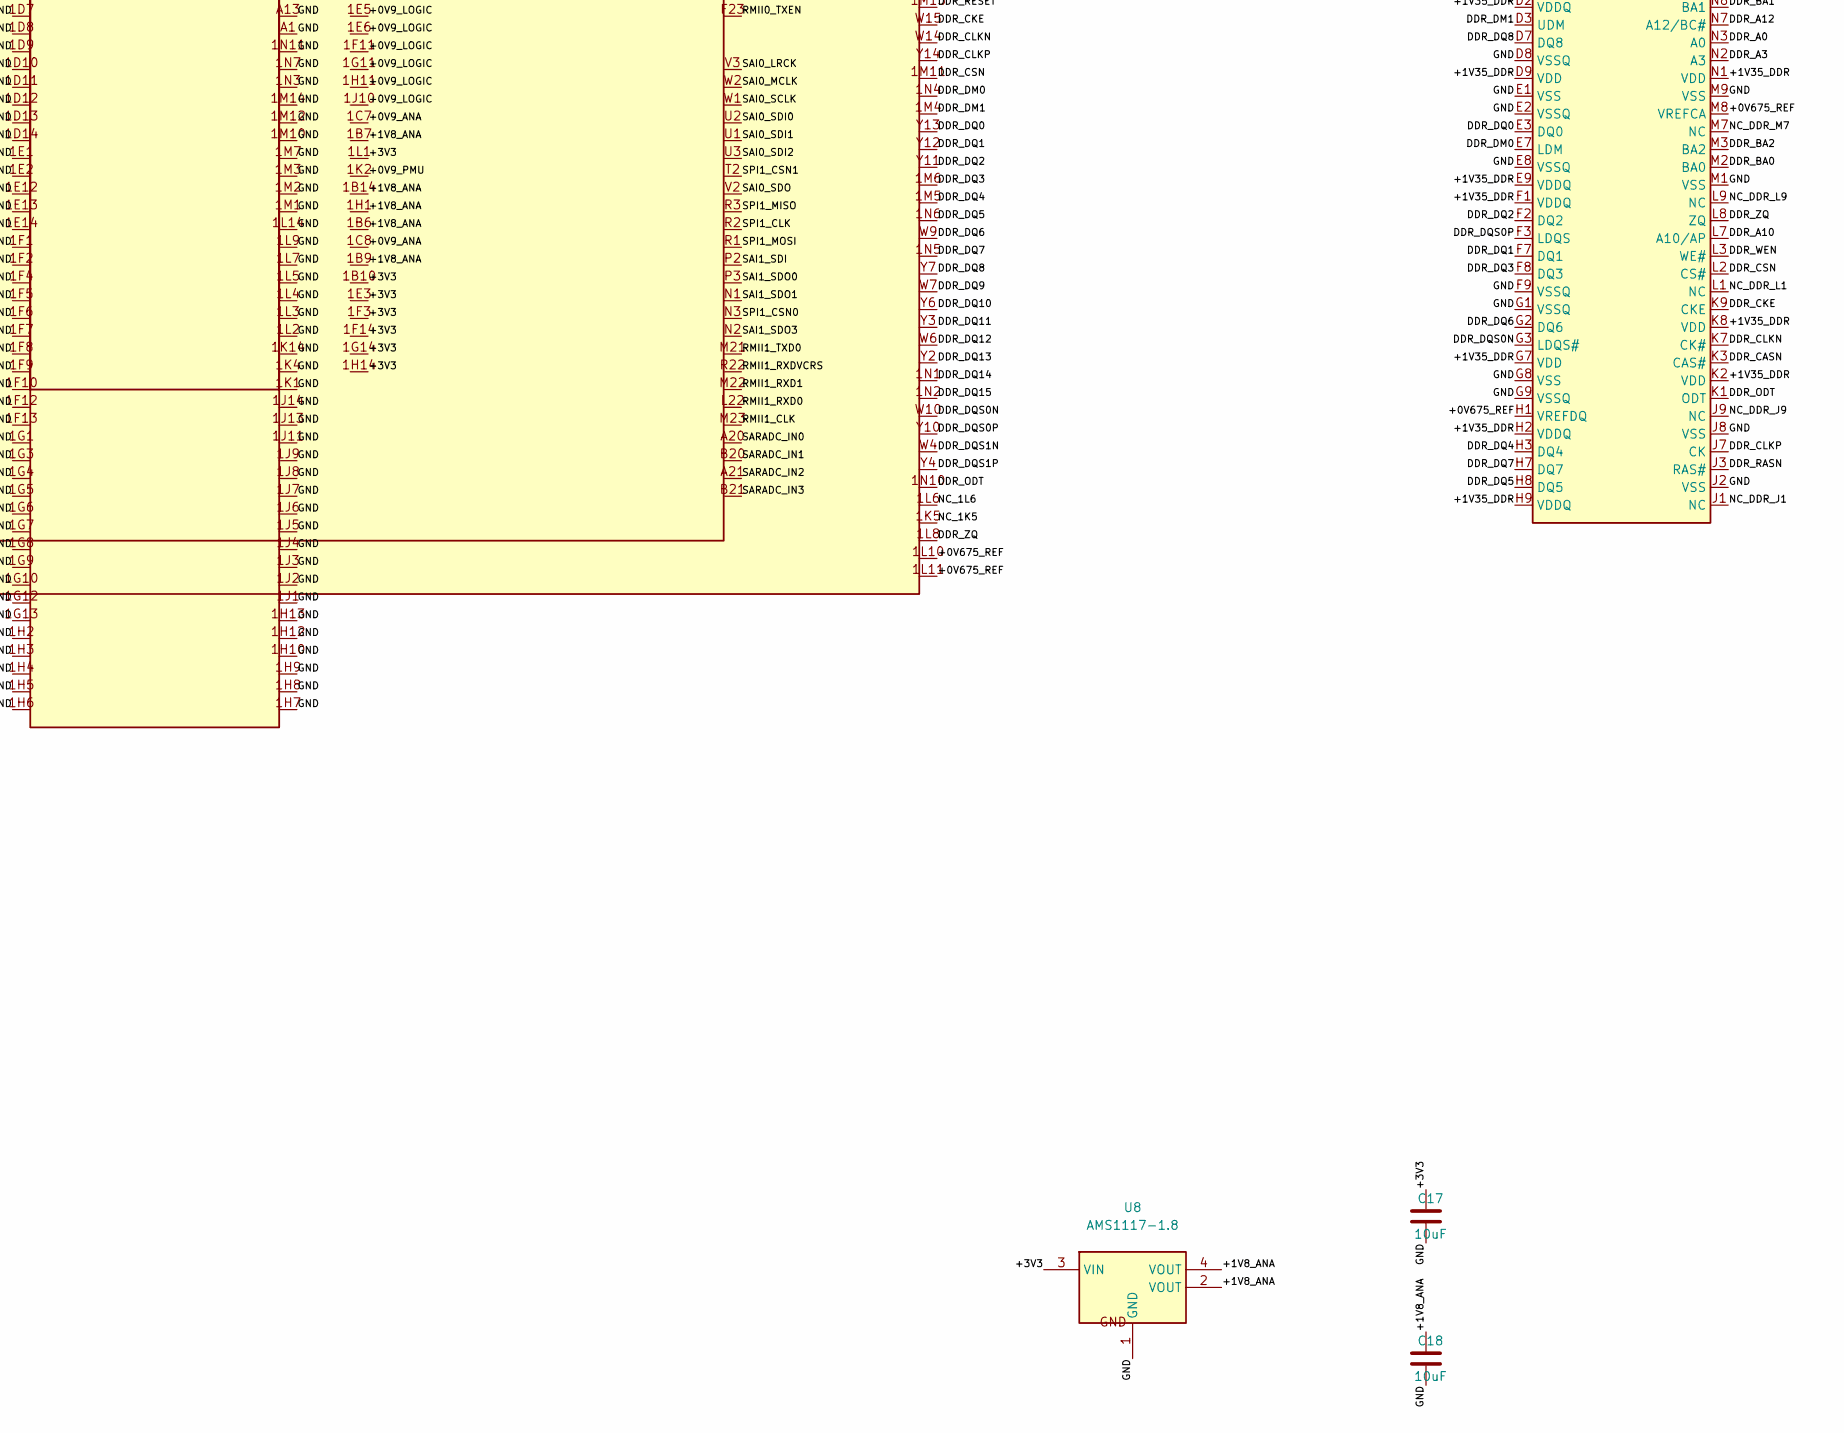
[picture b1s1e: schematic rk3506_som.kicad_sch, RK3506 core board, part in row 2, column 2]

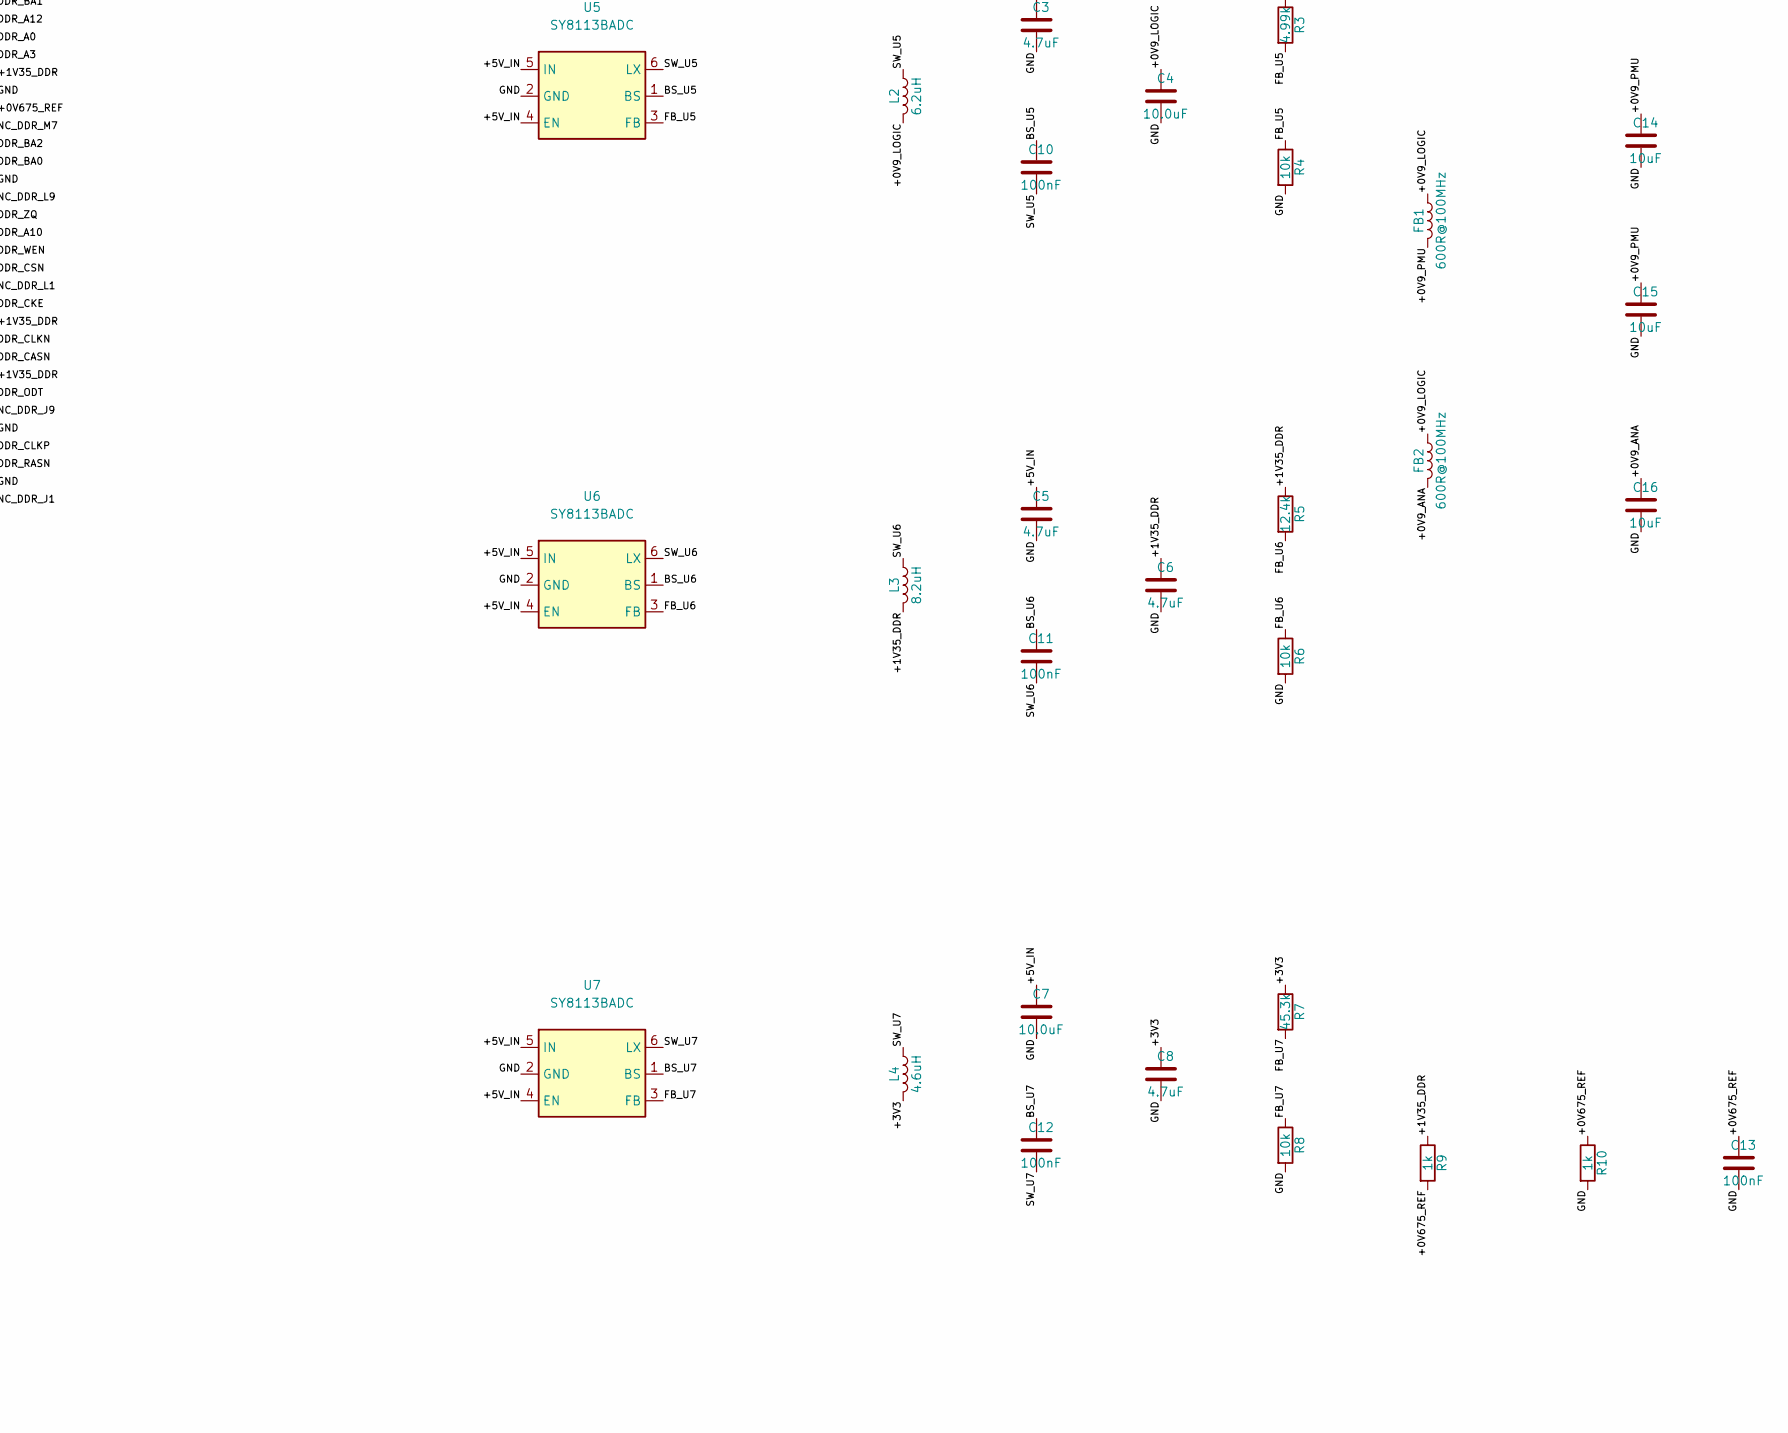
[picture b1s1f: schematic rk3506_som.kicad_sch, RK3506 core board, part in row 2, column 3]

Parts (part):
C1, C3, C5, C6, C8: 4.7uF; C_0402_1005Metric
C2, C4, C7: 10.0uF; C_0402_1005Metric
C9, C10, C11, C12, C13: 100nF; C_0402_1005Metric
C14, C15, C16, C17, C18: 10uF; C_0402_1005Metric
FB1, FB2: 600R@100MHz; L_0603_1608Metric
J1: SOM_CASTELLATION_140
L1: 4.3uH; L_Cenker_CKCS4020
L2: 6.2uH; L_Cenker_CKCS4020
L3: 8.2uH; L_Cenker_CKCS4020
L4: 4.6uH; L_Cenker_CKCS4020
R1: 5.9k; R_0402_1005Metric
R2, R4, R6, R8: 10k; R_0402_1005Metric
R3: 4.99k; R_0402_1005Metric
R5: 12.4k; R_0402_1005Metric
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
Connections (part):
/+0V9_ANA: C16.1, FB2.2, U1.1C7 (MIPI_DPHY_AVDD0V9), U1.1C8 (USB20_OTG_AVDD0V9)
/+0V9_CPU: C2.1, L1.2, R1.1, U1.1C2 (CPU_DVDD), U1.1C3 (CPU_DVDD), U1.1C4 (CPU_DVDD)
/+0V9_LOGIC: C4.1, FB1.1, FB2.1, L2.2, R3.1, U1.1E4 (LOGIC_DVDD), U1.1E5 (LOGIC_DVDD), U1.1E6 (LOGIC_DVDD), U1.1F11 (LOGIC_DVDD), U1.1G11 (LOGIC_DVDD), U1.1H11 (LOGIC_DVDD), U1.1J10 (LOGIC_DVDD)
/+0V9_PMU: C14.1, C15.1, FB1.2, U1.1K2 (PMU_LOGIC_DVDD0V9)
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
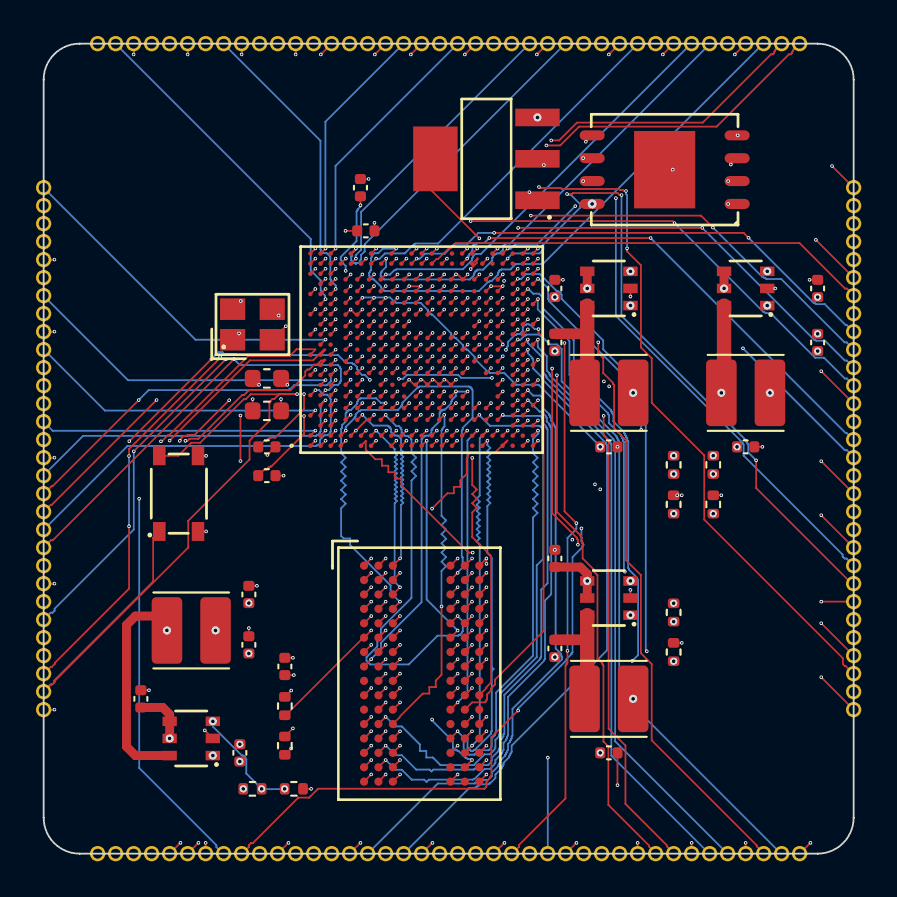
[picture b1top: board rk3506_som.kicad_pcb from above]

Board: 6 copper layers, 45.0 x 45.0 mm, 45 parts (0 on the bottom side), 175 nets.

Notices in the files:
README.md:
License:
这是 source-available，不是 OSI 认证的开源软件。** 二者不是措辞差别：OSI 开源许可不允许
限制使用领域，而这份许可明确禁止商业用途。
对象 | 许可 | 你可以 | 你不可以
源代码（`src/`、`run_server.py`、`tools/`、`tests/`、`skills/`…） | [PolyForm Noncommercial 1.0.0](LICENSE) | 个人使用、学习、研究、实验、教学、非营利/慈善/政府机构内部使用；修改；非商业分发（须带 `Required Notice` 与原许可全文） | **任何商业用途**（含内部商业流程、付费服务、商业产品集成）；再许可为其他许可
文档（`docs/` 与各 Markdown 正文） | [CC BY-NC-SA 4.0](https://creativecommons.org/licenses/by-nc-sa/4.0/deed.zh) | 署名、非商业地转载/改编、相同方式共享 | 商业使用；去掉署名；改用其他许可分发改编件
第三方组件 | 各自原许可（[THIRD-PARTY.md](THIRD-PARTY.md)） | 按原许可 | 按原许可
商业授权**：开 [Issue](https://gi
